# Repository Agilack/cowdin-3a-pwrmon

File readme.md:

CowDIN power monitor
====================

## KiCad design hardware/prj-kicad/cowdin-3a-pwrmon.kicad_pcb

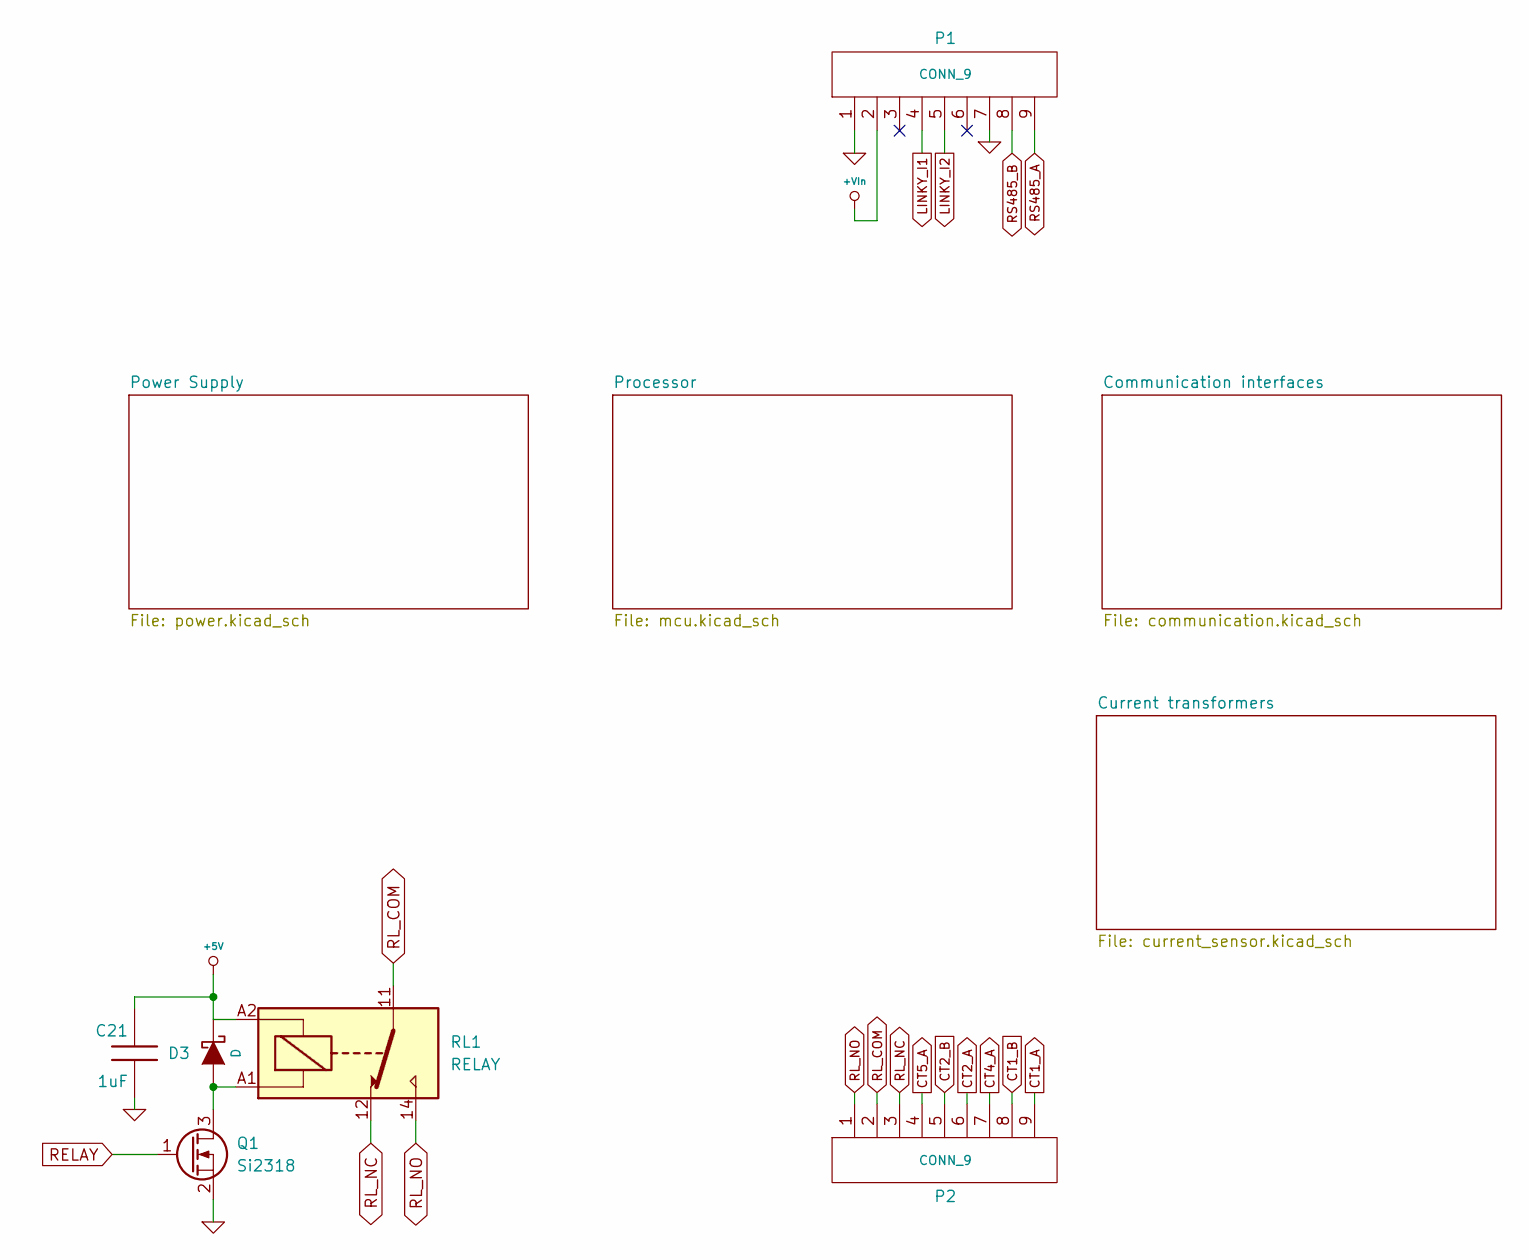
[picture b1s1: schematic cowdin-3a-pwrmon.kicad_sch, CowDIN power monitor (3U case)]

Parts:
C21: 1uF; SMD0603
D3: D; SOD-123
P1: CONN_9; CONN_WE2365_09
P2: CONN_9; CONN_WE2365_09r
Q1: Si2318; SOT23-3
RL1: RELAY; RL_3451

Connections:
+5V: C21.1, D3.2 (K), RL1.A2; also elsewhere on the board
+VIn: P1.2; also elsewhere on the board
CT1_A: P2.9; also elsewhere on the board
CT1_B: P2.8; also elsewhere on the board
CT2_A: P2.6; also elsewhere on the board
CT2_B: P2.5; also elsewhere on the board
CT4_A: P2.7; also elsewhere on the board
CT5_A: P2.4; also elsewhere on the board
GND: C21.2, P1.1, P1.7, Q1.2 (S); also elsewhere on the board
LINKY_I1: P1.4; also elsewhere on the board
LINKY_I2: P1.5; also elsewhere on the board
unnamed: D3.1 (A), Q1.3 (D), RL1.A1
RELAY: Q1.1 (G); also elsewhere on the board
RL_COM: P2.2, RL1.11
RL_NC: P2.3, RL1.12
RL_NO: P2.1, RL1.14
RS485_A: P1.9; also elsewhere on the board
RS485_B: P1.8; also elsewhere on the board

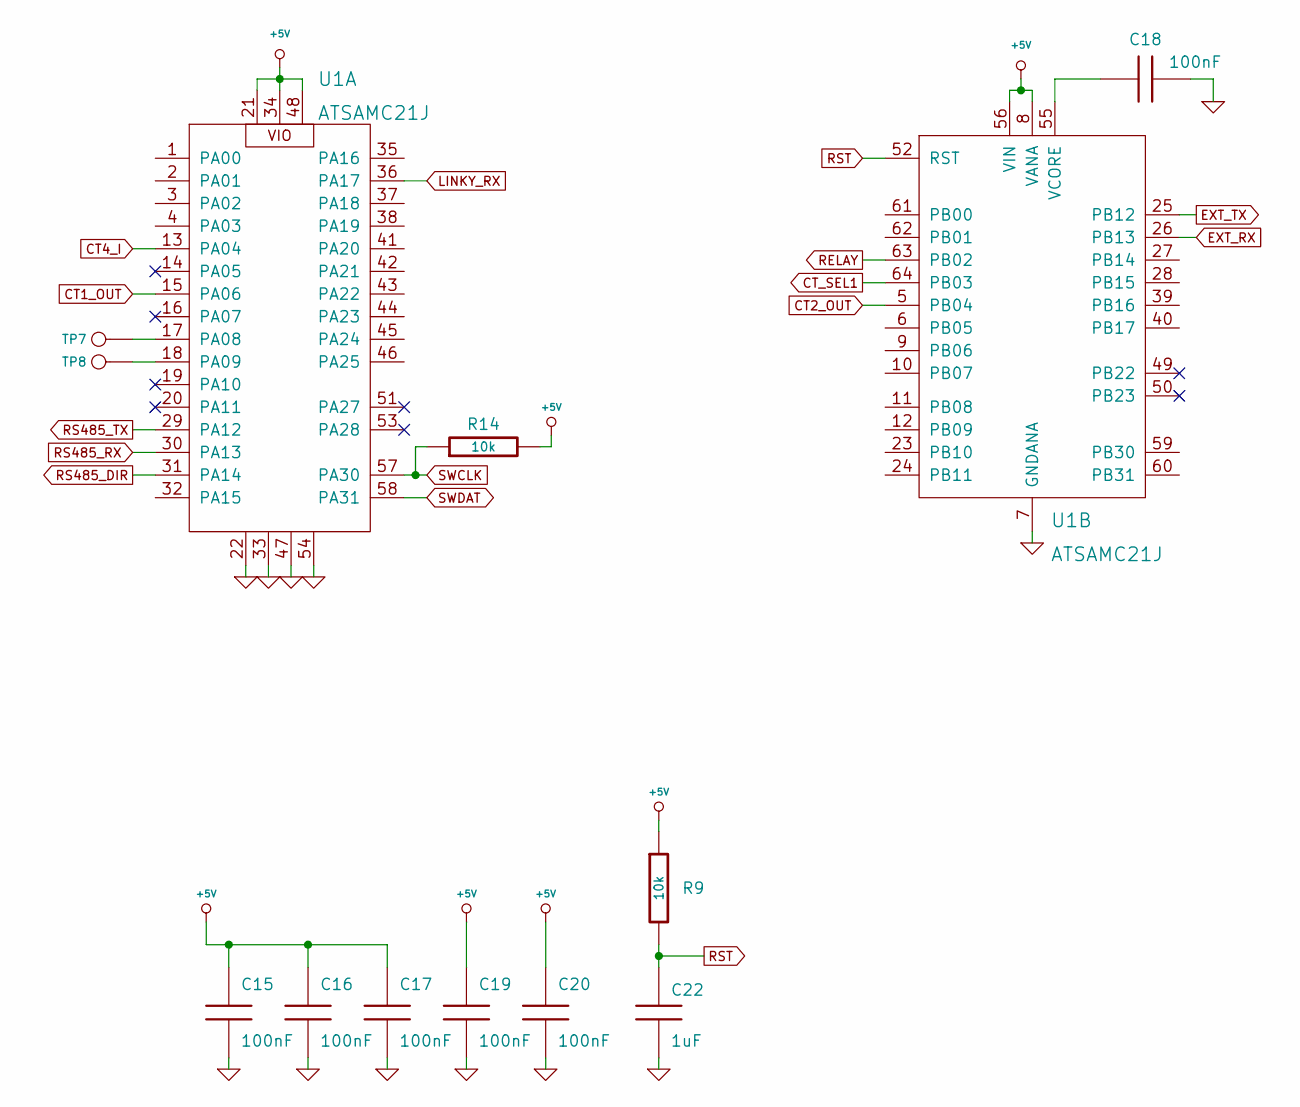
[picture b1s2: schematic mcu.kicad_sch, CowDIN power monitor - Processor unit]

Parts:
C15, C16, C17, C18, C19, C20: 100nF; SMD0603
C22: 1uF; SMD0603
R9, R14: 10k; SMD0603
TP7, TP8: CONN_1; TP_2SMD
U1: ATSAMC21J; TQFP64

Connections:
+5V: C15.1, C16.1, C17.1, C19.1, C20.1, R9.1, R14.2, U1.8 (VANA), U1.21, U1.34, U1.48, U1.56 (VIN); also elsewhere on the board
CT1_OUT: U1.15 (PA06); also elsewhere on the board
CT2_OUT: U1.5 (PB04); also elsewhere on the board
CT4_I: U1.13 (PA04); also elsewhere on the board
CT_SEL1: U1.64 (PB03); also elsewhere on the board
EXT_RX: U1.26 (PB13); also elsewhere on the board
EXT_TX: U1.25 (PB12); also elsewhere on the board
GND: C15.2, C16.2, C17.2, C18.2, C19.2, C20.2, C22.2, U1.7 (GNDANA), U1.22, U1.33, U1.47, U1.54; also elsewhere on the board
LINKY_RX: U1.36 (PA17); also elsewhere on the board
unnamed: C18.1, U1.55 (VCORE)
unnamed: TP7.1, U1.17 (PA08)
unnamed: TP8.1, U1.18 (PA09)
RELAY: U1.63 (PB02); also elsewhere on the board
RS485_DIR: U1.31 (PA14); also elsewhere on the board
RS485_RX: U1.30 (PA13); also elsewhere on the board
RS485_TX: U1.29 (PA12); also elsewhere on the board
RST: C22.1, R9.2, U1.52 (RST); also elsewhere on the board
SWCLK: R14.1, U1.57 (PA30); also elsewhere on the board
SWDAT: U1.58 (PA31); also elsewhere on the board

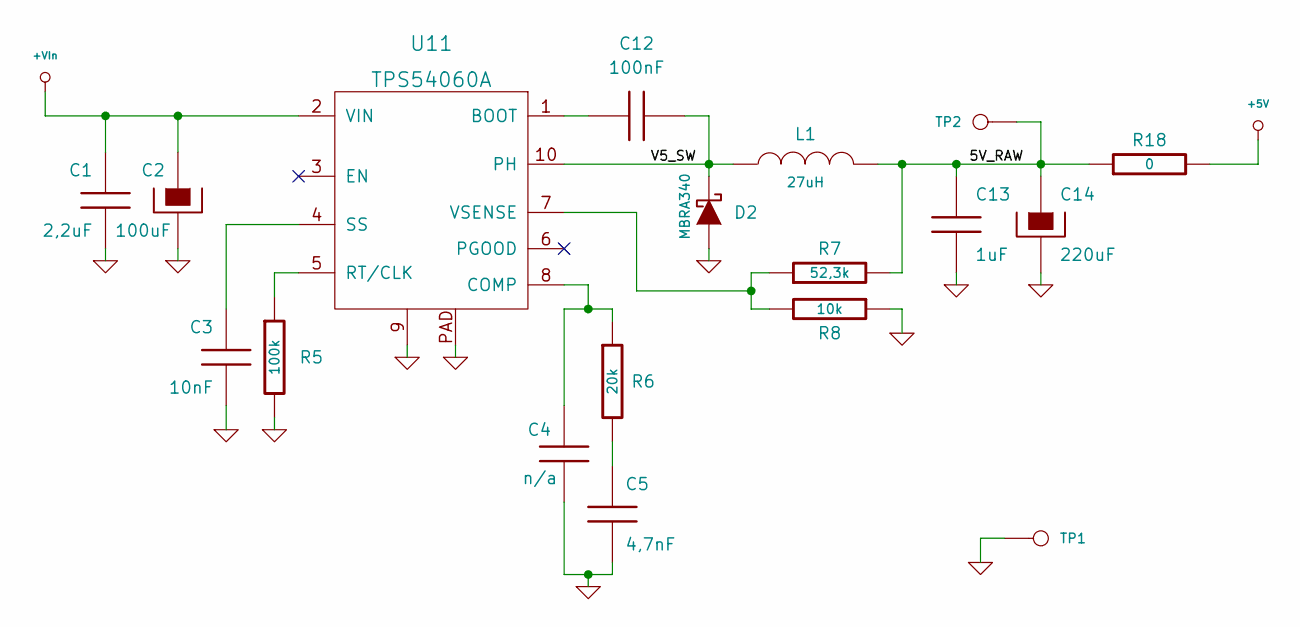
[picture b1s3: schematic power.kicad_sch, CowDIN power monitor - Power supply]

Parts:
C1: 2,2uF; SMD1206
C2: 100uF; C_ALU_8x10.5
C3: 10nF; SMD0603
C4: n/a; SMD0603
C5: 4,7nF; SMD0603
C12: 100nF; SMD0603
C13: 1uF; SMD0603
C14: 220uF; C_TPB_D4
D2: MBRA340; DO214AC
L1: 27uH; I_MSS1048
R5: 100k; SMD0603
R6: 20k; SMD0603
R7: 52,3k; SMD0603
R8: 10k; SMD0603
R18: 0; SMD1206
TP1, TP2: CONN_1; TP_SMD
U11: TPS54060A; MSOP10p

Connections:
+5V: R18.2; also elsewhere on the board
+VIn: C1.1, C2.1, U11.2 (VIN); also elsewhere on the board
/Power Supply/5V_RAW: C13.1, C14.1, L1.2, R7.2, R18.1, TP2.1
/Power Supply/V5_SW: C12.2, D2.2 (K), L1.1, U11.10 (PH)
GND: C1.2, C2.2, C3.2, C4.2, C5.2, C13.2, C14.2, D2.1 (A), R5.2, R8.1, TP1.1, U11.9, U11.PAD; also elsewhere on the board
unnamed: C3.1, U11.4 (SS)
unnamed: C4.1, R6.1, U11.8 (COMP)
unnamed: C5.1, R6.2
unnamed: C12.1, U11.1 (BOOT)
unnamed: R5.1, U11.5 (RT/CLK)
unnamed: R7.1, R8.2, U11.7 (VSENSE)

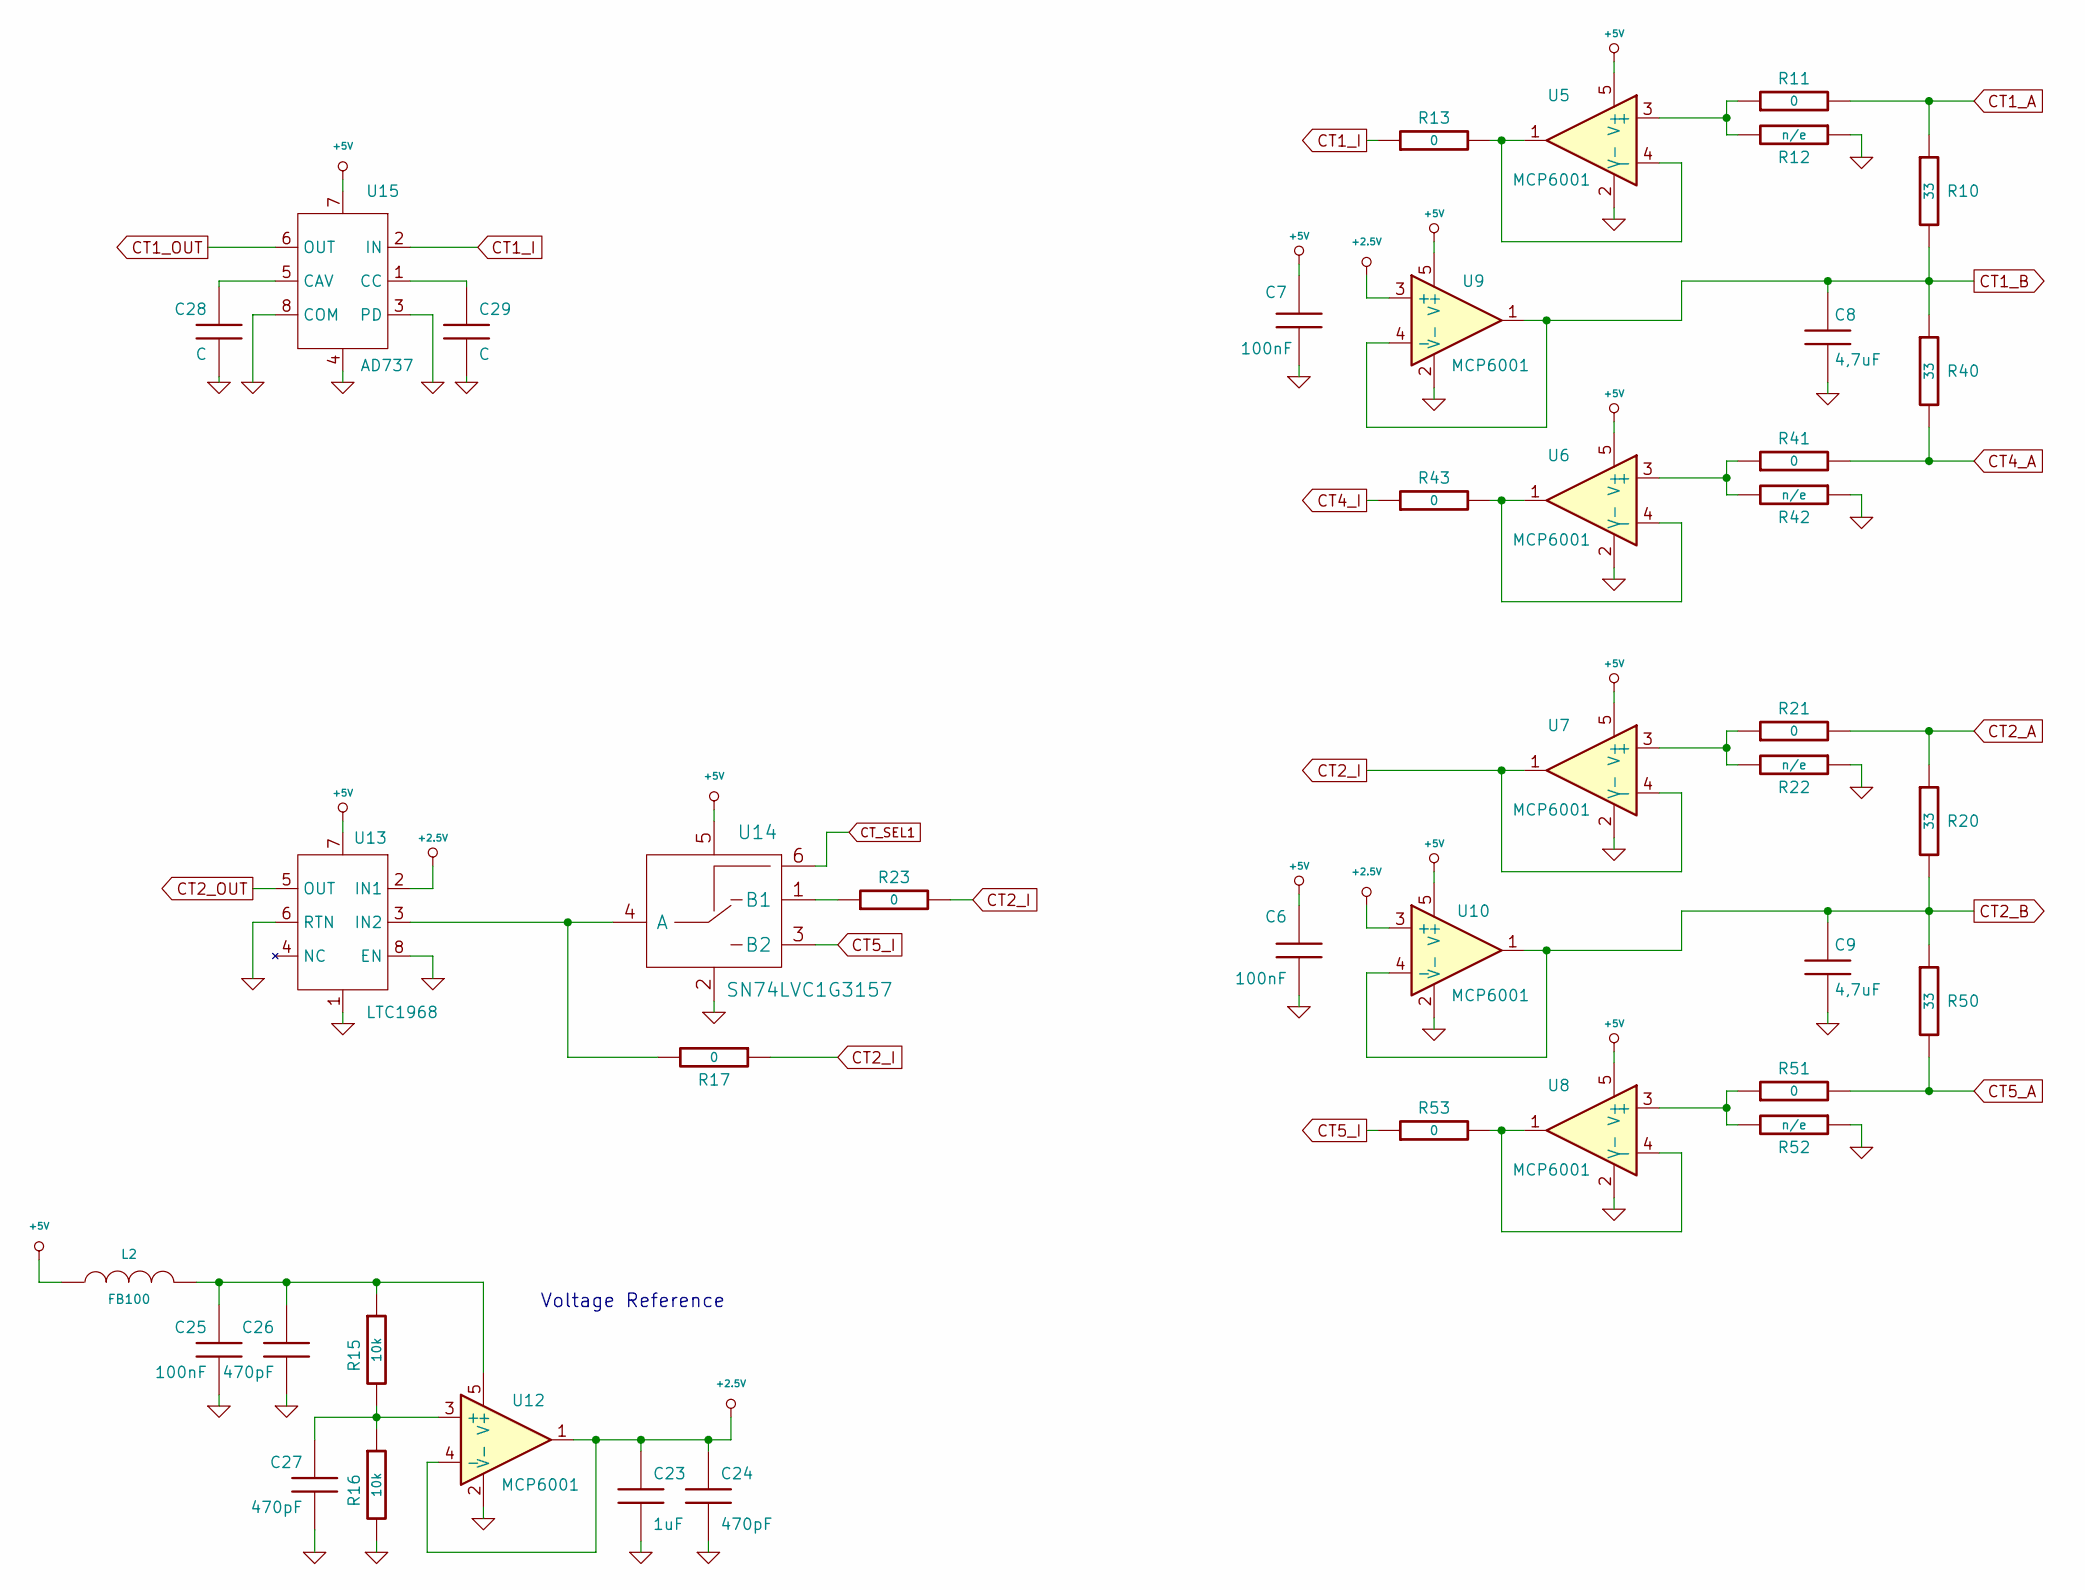
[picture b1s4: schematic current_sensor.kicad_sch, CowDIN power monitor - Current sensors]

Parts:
C6, C7, C25: 100nF; SMD0603
C8, C9: 4,7uF; SMD0805
C23: 1uF; SMD0603
C24, C26, C27: 470pF; SMD0603
C28, C29: C; SMD0603
L2: FB100; SMD0603
R10, R20, R40, R50: 33; SMD2010
R11, R13, R17, R21, R23, R41, R43, R51, R53: 0; SMD0603
R12, R22, R42, R52: n/e; SMD0603
R15, R16: 10k; SMD0603
U5, U6, U7, U8, U9, U10, U12: MCP6001; SOT23-5
U13: LTC1968; MSOP-8
U14: SN74LVC1G3157; SC70-6
U15: AD737; SOIC-8E

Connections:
+2.5V: C23.1, C24.1, U9.3 (+), U10.3 (+), U12.1, U12.4 (-), U13.2 (IN1)
+5V: C6.1, C7.1, L2.1, U5.5 (V+), U6.5 (V+), U7.5 (V+), U8.5 (V+), U9.5 (V+), U10.5 (V+), U13.7, U14.5, U15.7; also elsewhere on the board
CT1_A: R10.1, R11.2; also elsewhere on the board
CT1_B: C8.1, R10.2, R40.1, U9.1, U9.4 (-); also elsewhere on the board
CT1_I: R13.1, U15.2 (IN)
CT1_OUT: U15.6 (OUT); also elsewhere on the board
CT2_A: R20.1, R21.2; also elsewhere on the board
CT2_B: C9.1, R20.2, R50.1, U10.1, U10.4 (-); also elsewhere on the board
CT2_I: R17.1, R23.2, U7.1, U7.4 (-)
CT2_OUT: U13.5 (OUT); also elsewhere on the board
CT4_A: R40.2, R41.2; also elsewhere on the board
CT4_I: R43.1; also elsewhere on the board
CT5_A: R50.2, R51.2; also elsewhere on the board
CT5_I: R53.1, U14.3 (B2)
CT_SEL1: U14.6; also elsewhere on the board
GND: C6.2, C7.2, C8.2, C9.2, C23.2, C24.2, C25.2, C26.2, C27.2, C28.2, C29.2, R12.1, R16.2, R22.1, R42.1, R52.1, U5.2 (V-), U6.2 (V-), U7.2 (V-), U8.2 (V-), U9.2 (V-), U10.2 (V-), U12.2 (V-), U13.1, U13.6 (RTN), U13.8 (EN), U14.2, U15.3 (PD), U15.4, U15.8 (COM); also elsewhere on the board
unnamed: C25.1, C26.1, L2.2, R15.1, U12.5 (V+)
unnamed: C27.1, R15.2, R16.1, U12.3 (+)
unnamed: C28.1, U15.5 (CAV)
unnamed: C29.1, U15.1 (CC)
unnamed: R11.1, R12.2, U5.3 (+)
unnamed: R13.2, U5.1, U5.4 (-)
unnamed: R17.2, U13.3 (IN2), U14.4 (A)
unnamed: R21.1, R22.2, U7.3 (+)
unnamed: R23.1, U14.1 (B1)
unnamed: R41.1, R42.2, U6.3 (+)
unnamed: R43.2, U6.1, U6.4 (-)
unnamed: R51.1, R52.2, U8.3 (+)
unnamed: R53.2, U8.1, U8.4 (-)

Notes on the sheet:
Voltage Reference

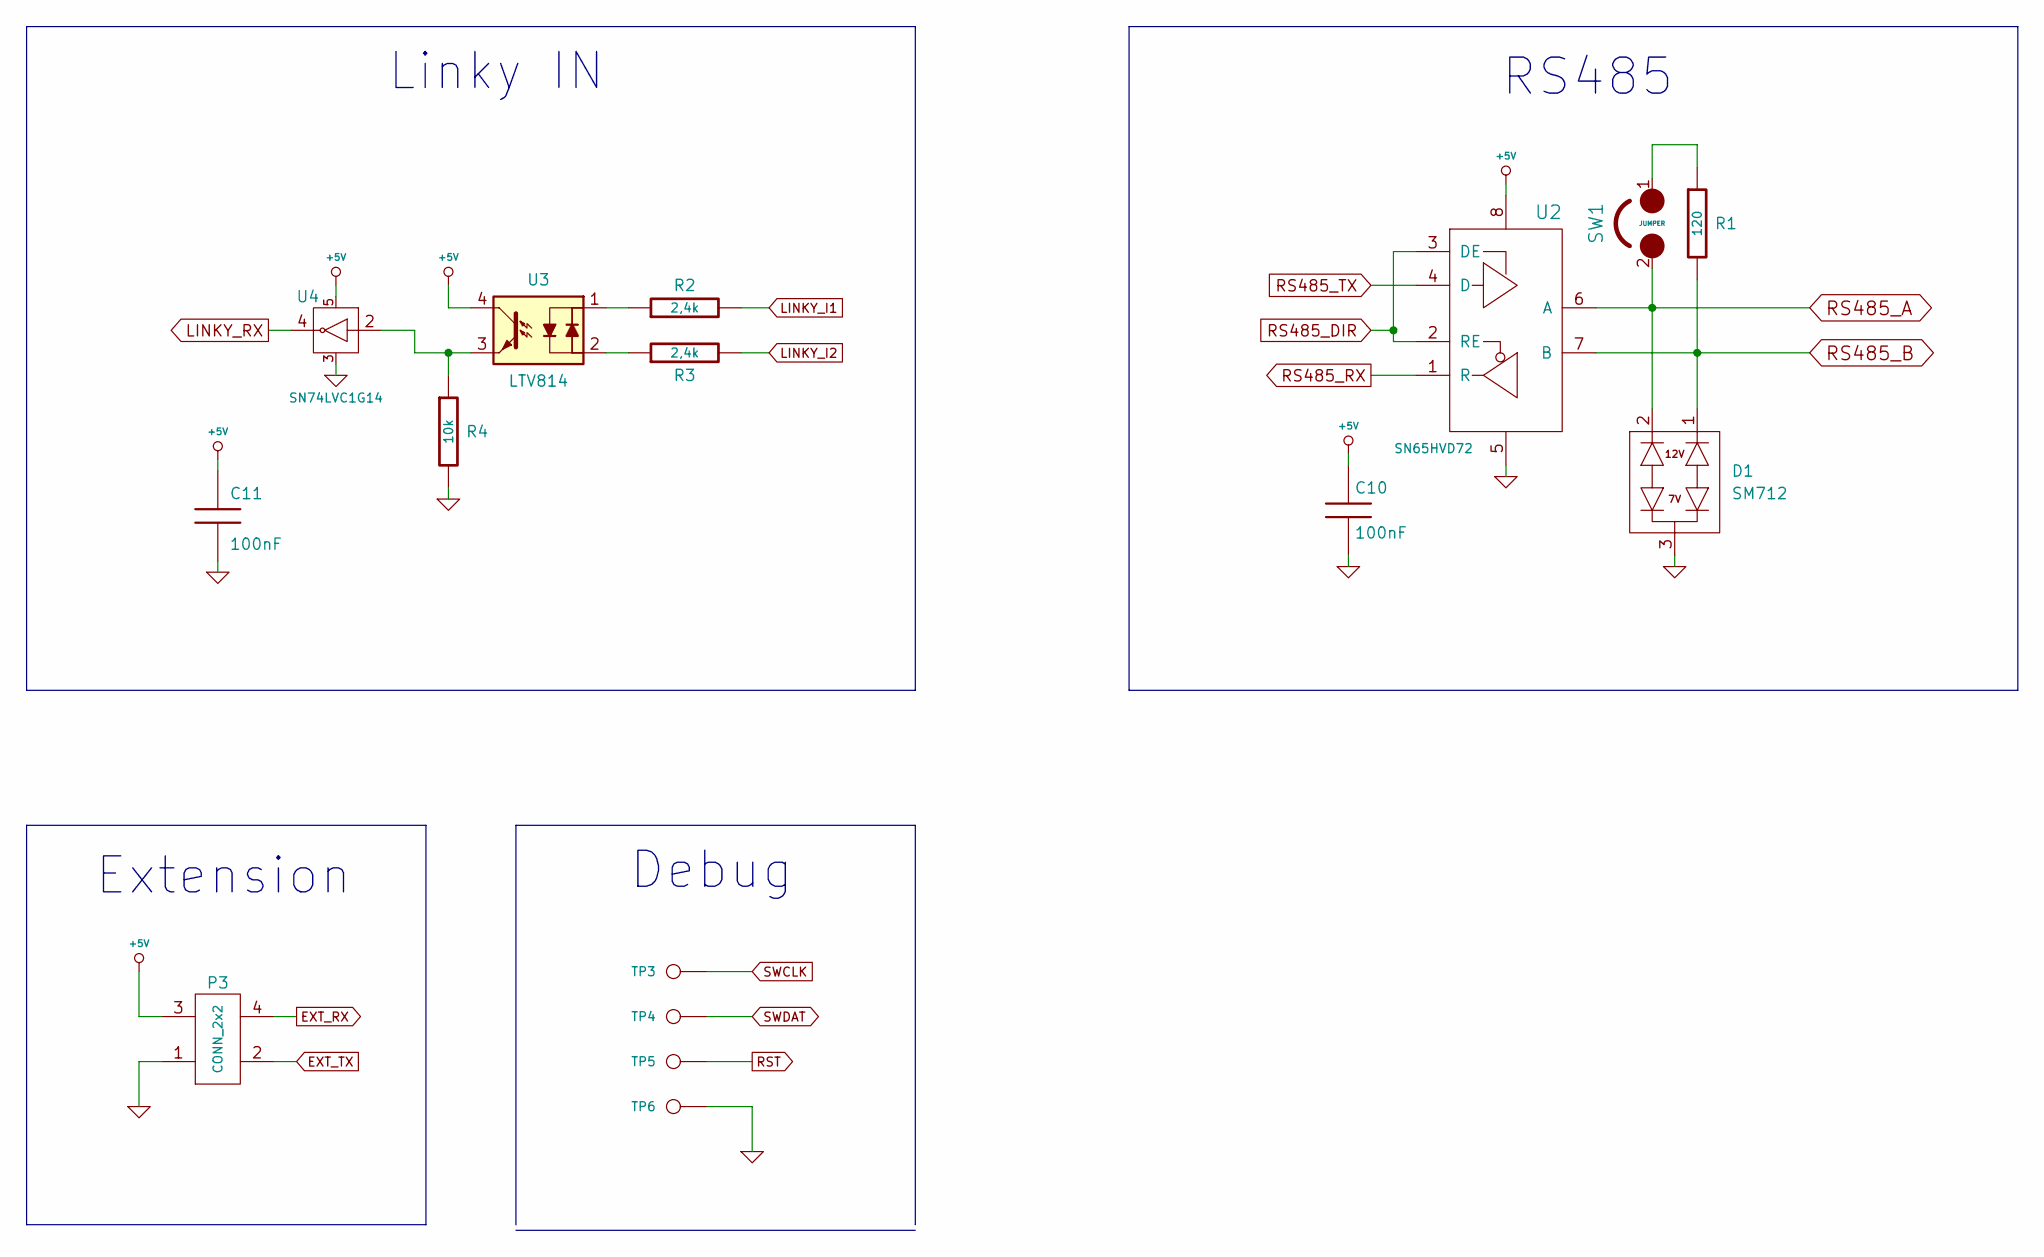
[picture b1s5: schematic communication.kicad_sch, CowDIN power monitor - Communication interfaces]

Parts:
C10, C11: 100nF; SMD0603
D1: SM712; SOT23-3
P3: CONN_2x2; CONN_SMD2x2
R1: 120; SMD1206
R2, R3: 2,4k; SMD0805
R4: 10k; SMD0603
SW1: JUMPER; SW_450301014042
TP3, TP4, TP5, TP6: CONN_1; TP_SMD
U2: SN65HVD72; SOIC-8E
U3: LTV814; SMD4
U4: SN74LVC1G14; SOT23-5

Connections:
+5V: C10.1, C11.1, P3.3, U2.8, U3.4, U4.5; also elsewhere on the board
EXT_RX: P3.4; also elsewhere on the board
EXT_TX: P3.2 (PM); also elsewhere on the board
GND: C10.2, C11.2, D1.3, P3.1, R4.2, TP6.1, U2.5, U4.3; also elsewhere on the board
LINKY_I1: R2.2; also elsewhere on the board
LINKY_I2: R3.2; also elsewhere on the board
LINKY_RX: U4.4 (Y); also elsewhere on the board
unnamed: R1.1, SW1.1
unnamed: R2.1, U3.1
unnamed: R3.1, U3.2
unnamed: R4.1, U3.3, U4.2 (A)
RS485_A: D1.2, SW1.2, U2.6 (A); also elsewhere on the board
RS485_B: D1.1, R1.2, U2.7 (B); also elsewhere on the board
RS485_DIR: U2.2 (RE), U2.3 (DE); also elsewhere on the board
RS485_RX: U2.1 (R); also elsewhere on the board
RS485_TX: U2.4 (D); also elsewhere on the board
RST: TP5.1; also elsewhere on the board
SWCLK: TP3.1; also elsewhere on the board
SWDAT: TP4.1; also elsewhere on the board

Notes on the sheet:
Linky IN
RS485
Extension
Debug

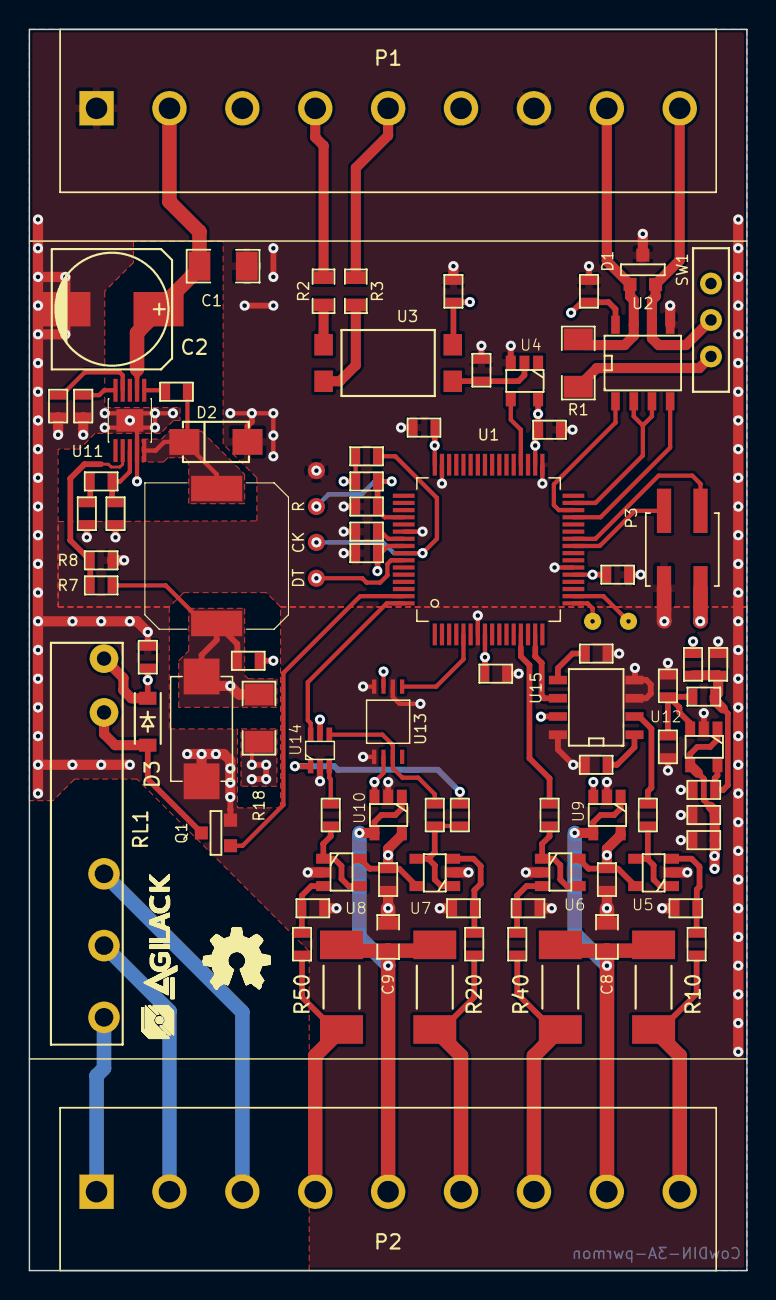
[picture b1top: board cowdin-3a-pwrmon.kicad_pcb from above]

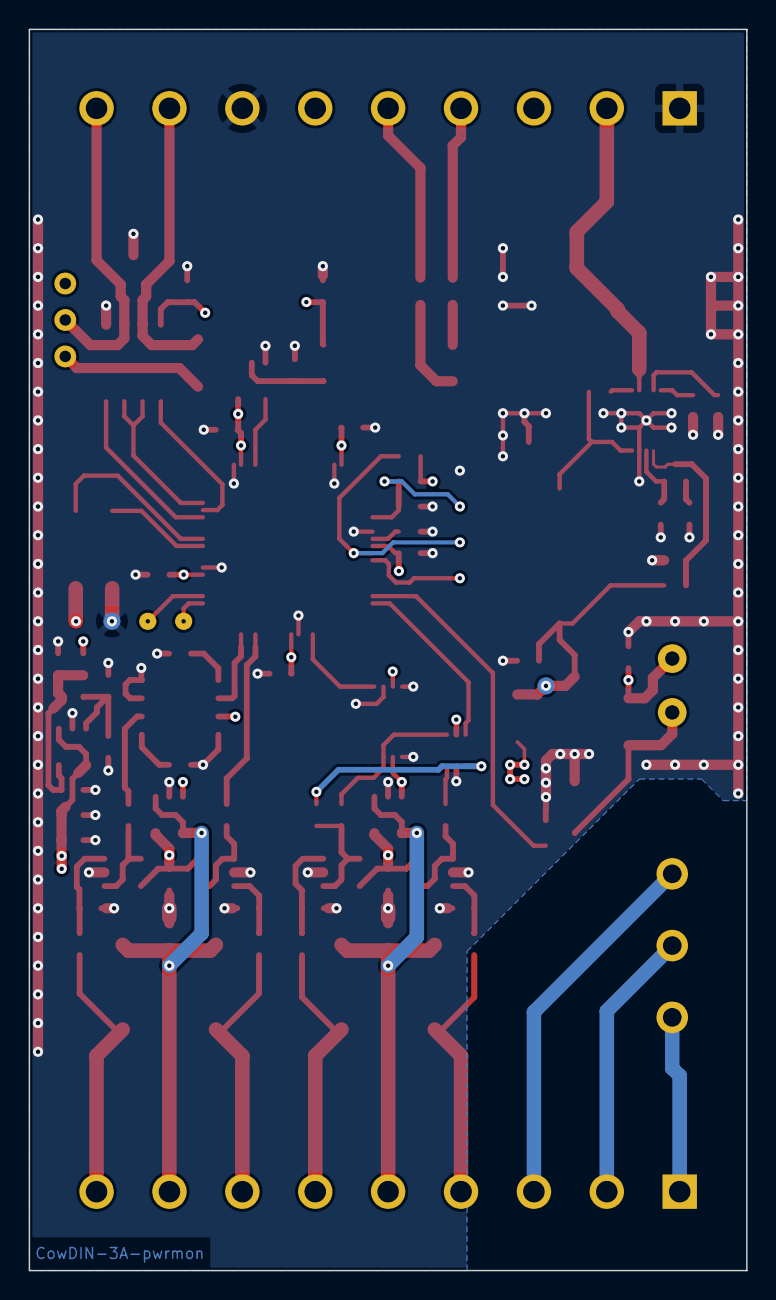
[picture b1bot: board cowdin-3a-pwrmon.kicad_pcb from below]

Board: 4 copper layers, 50.0 x 86.5 mm, 95 parts (2 on the bottom side), 63 nets.

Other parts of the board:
agilack-11.5: 450px; logo-agilack-11.5
ohw_logo: VAL**; logo-ohw

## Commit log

2022-04-12 --=={ Create project skeleton }==--
2022-04-13 Hardware: Add communication interfaces (RS485 and Linky)
2022-04-14 Hardware: Add power supply
2022-04-15 Hardware: Add processor (ATMSAMC21) and relay option
2022-04-16 Hardware: Finish current sensor interface and create production files for rev1

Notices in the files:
hardware/prj-kicad/communication.kicad_sch:
License: CC-by-SA
